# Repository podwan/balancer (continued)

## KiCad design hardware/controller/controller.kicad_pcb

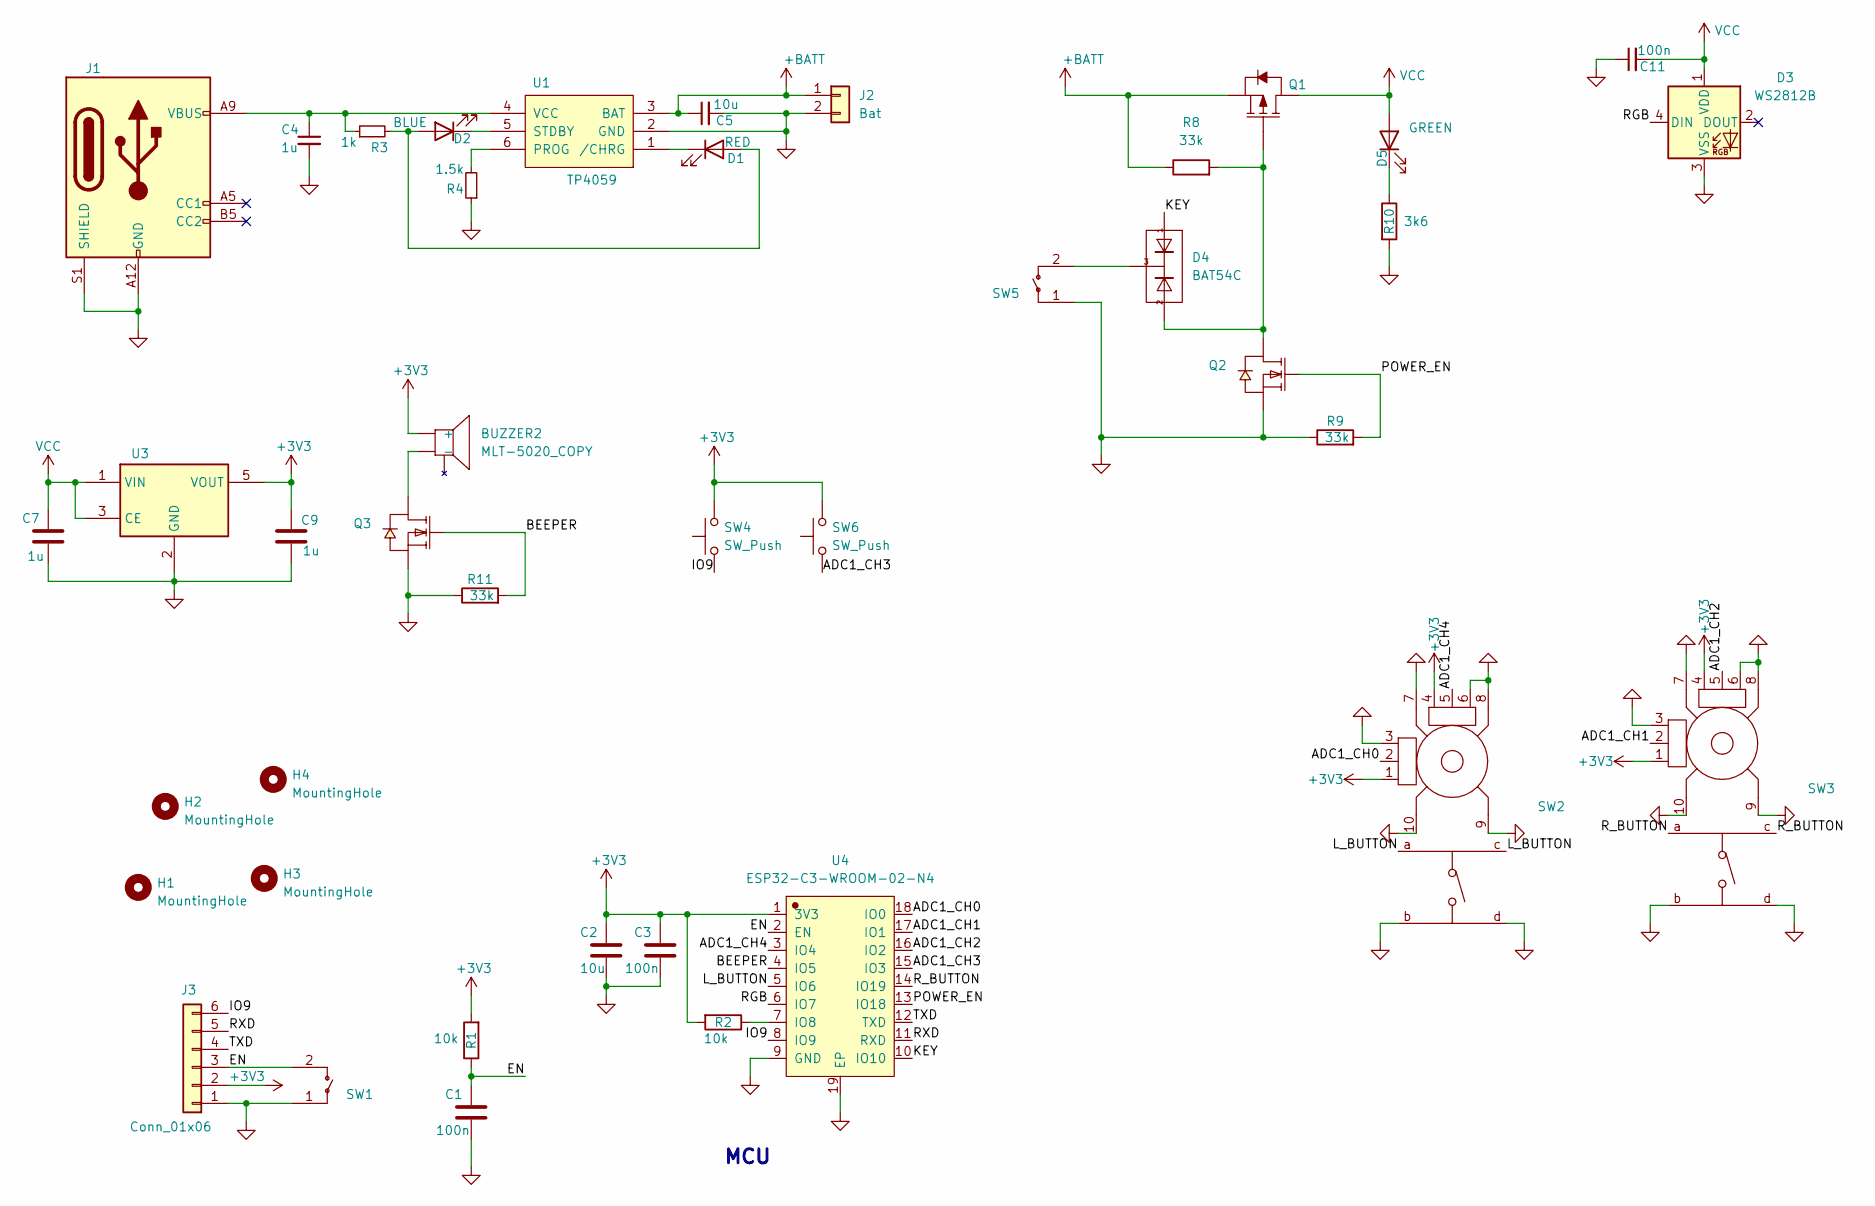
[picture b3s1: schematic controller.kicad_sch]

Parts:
BUZZER2: MLT-5020_COPY; BUZ-SMD_L5.0-W5.5-P4.60
C1, C3, C11: 100n; C_0603_1608Metric_Pad1.08x0.95mm_HandSolder
C2, C5: 10u; C_0805_2012Metric_Pad1.18x1.45mm_HandSolder
C4, C7, C9: 1u; C_0603_1608Metric_Pad1.08x0.95mm_HandSolder
D1: RED; LED_0603_1608Metric_Pad1.05x0.95mm_HandSolder
D2: BLUE; LED_0603_1608Metric_Pad1.05x0.95mm_HandSolder
D3: WS2812B; LED_WS2812B_PLCC4_5.0x5.0mm_P3.2mm
D4: BAT54C; SOT-23
D5: GREEN; LED_0603_1608Metric_Pad1.05x0.95mm_HandSolder
H1, H2, H3, H4: MountingHole; MountingHole_2.2mm_M2_Pad
J1: USB_C_Receptacle_PowerOnly_6P; USB-C-SMD_HX-TYPE-C-6PIN
J2: Bat; CONN-SMD_2P-P2.54-XH2.54-WT
J3: Conn_01x06; CONN-SMD_6P-P1.00_XYECONN_XY-SH1.0-6A61
Q1: AO3401; SOT-23
Q2, Q3: AllPower__AP2300; SOT-23
R1, R2: 10k; R_0603_1608Metric_Pad0.98x0.95mm_HandSolder
R3: 1k; R_0603_1608Metric_Pad0.98x0.95mm_HandSolder
R4: 1.5k; R_0603_1608Metric_Pad0.98x0.95mm_HandSolder
R8, R9, R11: 33k; R_0603_1608Metric_Pad0.98x0.95mm_HandSolder
R10: 3k6; R_0603_1608Metric_Pad0.98x0.95mm_HandSolder
SW1, SW5: TS-1199A-B-B; SW-SMD_L6.0-W6.0-P6.00-LS6.6
SW2, SW3: RKJXV1224005; SW-TH_RKJXV1224005
SW4, SW6: SW_Push
U1: TP4059; SOT-23-6_L2.9-W1.6-P0.95-LS2.8-BR
U3: XC6220B331MR; SOT-23-5
U4: ESP32-C3-WROOM-02-N4; ESP32-C3-WROOM-02

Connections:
+3V3: BUZZER2.1 (+), C2.1, C3.1, C9.1, J3.2, R1.2, R2.2, SW2.1 (B), SW2.4 (A), SW3.1 (B), SW3.4 (A), SW4.2, SW6.2, U3.5 (VOUT), U4.1 (3V3)
+BATT: C5.1, J2.1, Q1.2 (S), R8.1, U1.3 (BAT)
/ADC1_CH0: SW2.2 (DTA), U4.18 (IO0)
/ADC1_CH1: SW3.2 (DTA), U4.17 (IO1)
/ADC1_CH2: SW3.5 (DTA), U4.16 (IO2)
/ADC1_CH3: SW6.1, U4.15 (IO3)
/ADC1_CH4: SW2.5 (DTA), U4.3 (IO4)
/BEEPER: Q3.1 (G), R11.2, U4.4 (IO5)
/EN: C1.1, J3.3, R1.1, SW1.2, U4.2 (EN)
/IO9: J3.6, SW4.1, U4.8 (IO9)
/KEY: D4.1 (A), U4.10 (IO10)
/L_BUTTON: SW2.a, SW2.c, U4.5 (IO6)
/POWER_EN: Q2.1 (G), R9.2, U4.13 (IO18)
/RGB: D3.4 (DIN), U4.6 (IO7)
/RXD: J3.5, U4.11 (RXD)
/R_BUTTON: SW3.a, SW3.c, U4.14 (IO19)
/TXD: J3.4, U4.12 (TXD)
GND: C1.2, C2.2, C3.2, C4.2, C5.2, C7.2, C9.2, C11.1, D3.3 (VSS), J1.A12 (GND), J1.B12 (GND), J1.S1 (SHIELD), J2.2, J3.1, Q2.2 (S), Q3.2 (S), R4.1, R9.1, R10.2, R11.1, SW1.1, SW2.3 (A), SW2.6 (B), SW2.7 (GND), SW2.8 (GND), SW2.9 (GND), SW2.10 (GND), SW2.b, SW2.d, SW3.3 (A), SW3.6 (B), SW3.7 (GND), SW3.8 (GND), SW3.9 (GND), SW3.10 (GND), SW3.b, SW3.d, SW5.1, U1.2 (GND), U3.2 (GND), U4.9 (GND), U4.19 (EP)
unnamed: BUZZER2.2 (-), Q3.3 (D)
unnamed: D1.2 (A), D2.2 (A), R3.2
unnamed: D1.1 (K), U1.1 (/CHRG)
unnamed: D2.1 (K), U1.5 (STDBY)
unnamed: D4.3 (C), SW5.2
unnamed: D5.1 (K), R10.1
unnamed: D4.2 (A), Q1.1 (G), Q2.3 (D), R8.2
unnamed: R4.2, U1.6 (PROG)
unnamed: C4.1, J1.A9 (VBUS), J1.B9 (VBUS), R3.1, U1.4 (VCC)
unnamed: R2.1, U4.7 (IO8)
VCC: C7.1, C11.2, D3.1 (VDD), D5.2 (A), Q1.3 (D), U3.1 (VIN), U3.3 (CE)

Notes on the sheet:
MCU

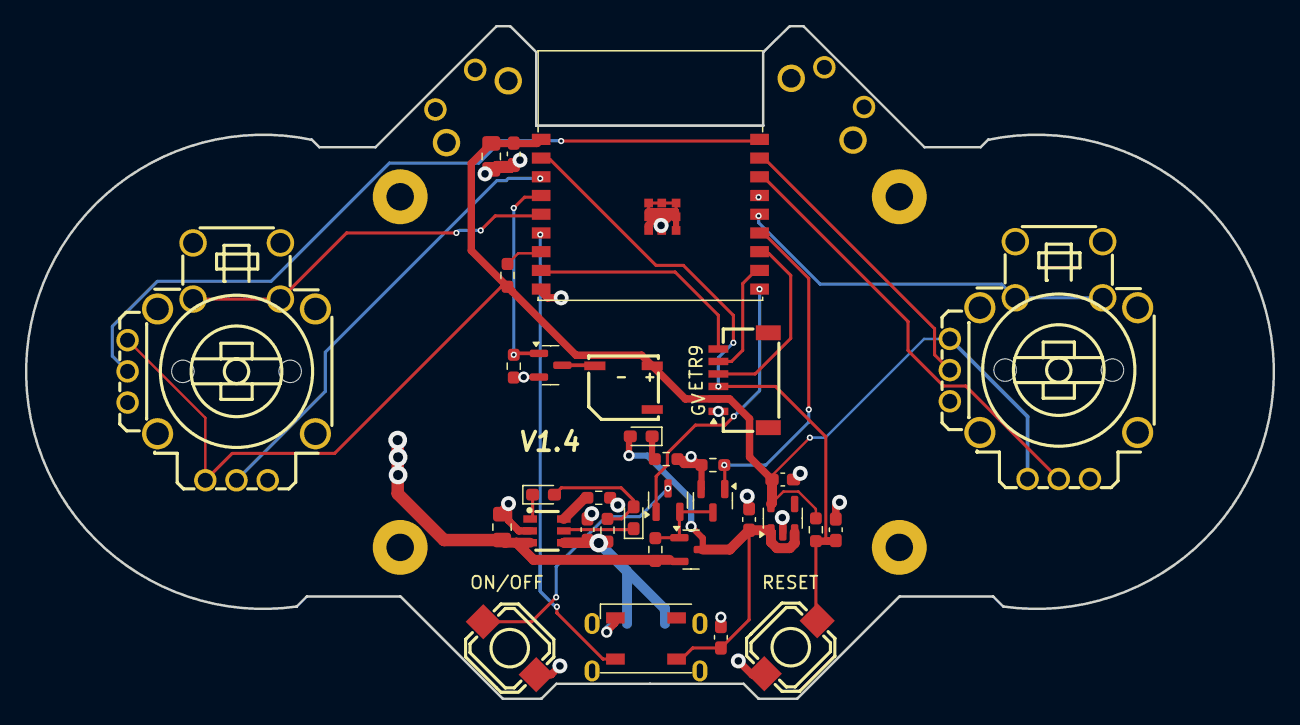
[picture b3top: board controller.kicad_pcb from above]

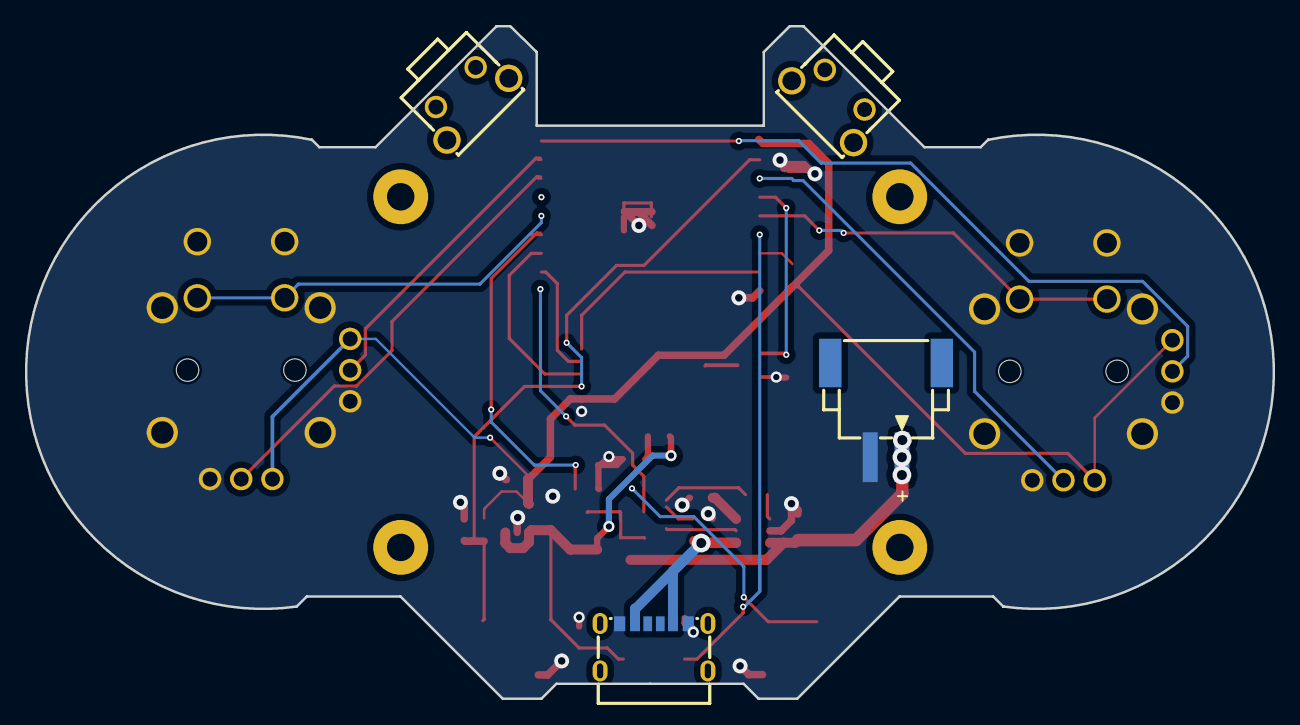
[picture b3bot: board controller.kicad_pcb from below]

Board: 2 copper layers, 100.0 x 53.9 mm, 41 parts (4 on the bottom side), 29 nets.

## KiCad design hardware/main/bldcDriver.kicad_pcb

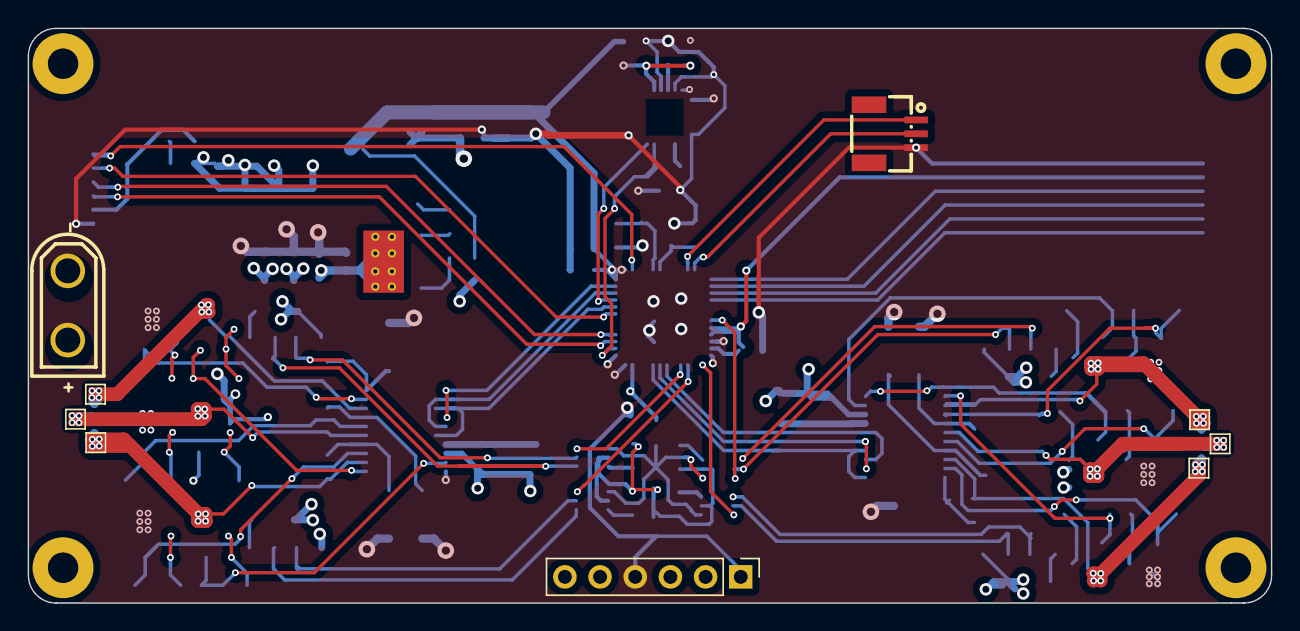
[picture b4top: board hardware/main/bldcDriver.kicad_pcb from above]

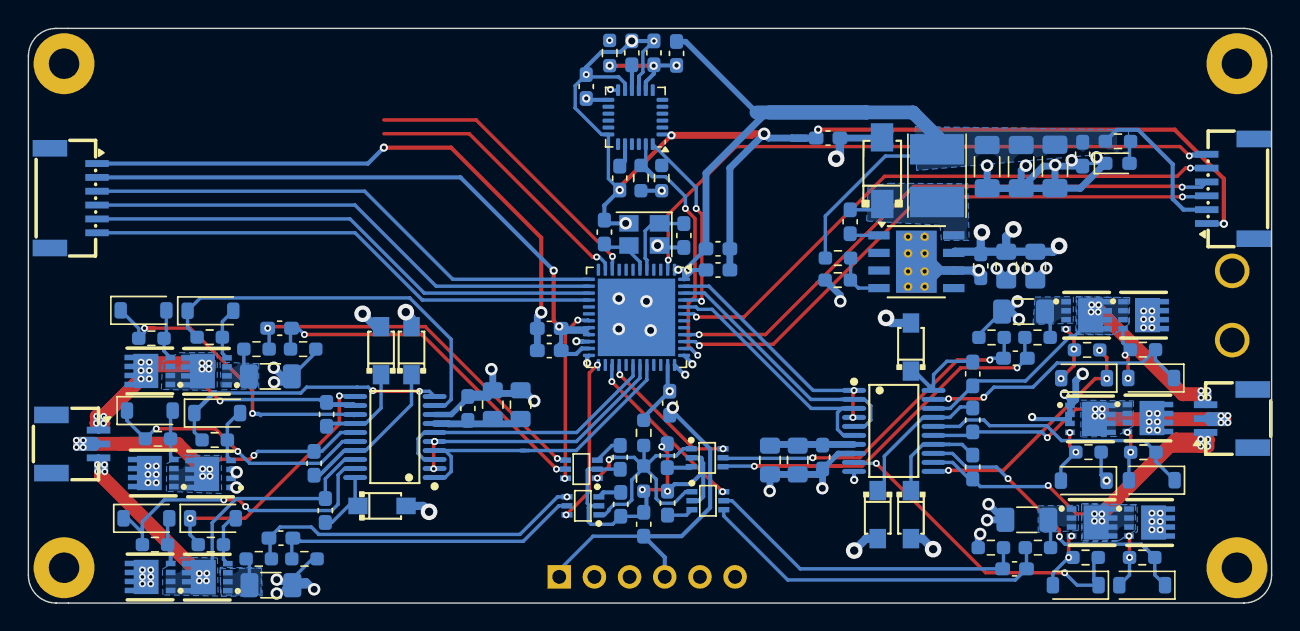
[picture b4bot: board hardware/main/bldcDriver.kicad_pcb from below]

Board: 4 copper layers, 89.8 x 41.5 mm, 130 parts (121 on the bottom side), 96 nets.

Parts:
C1, C13: 10n; C_0603_1608Metric_Pad1.08x0.95mm_HandSolder
C2, C3, C4: 47u; C_1206_3216Metric_Pad1.33x1.80mm_HandSolder
C5, C6, C12, C14, C33, C34: 22u; C_0805_2012Metric_Pad1.18x1.45mm_HandSolder
C7, C8, C9, C10, C11, C15, C16, C17, C18, C19, C20, C22, C23, C25, C26, C27, C29, C30, C31, C32: 100n; C_0603_1608Metric_Pad1.08x0.95mm_HandSolder
C21: 470n; C_0603_1608Metric_Pad1.08x0.95mm_HandSolder
C24: 2.2n; C_0603_1608Metric_Pad1.08x0.95mm_HandSolder
C28, C35, C36, C37: 1n; C_0603_1608Metric_Pad1.08x0.95mm_HandSolder
C67, C68: 12p; C_0603_1608Metric_Pad1.08x0.95mm_HandSolder
CN1, CN2: MR30PW-F; CONN-SMD_3P-P1.00_BX-SH1.0-3PWT
D1: LED; LED_0603_1608Metric_Pad1.05x0.95mm_HandSolder
D2, D3, D4, D7, D10, D11: D; SOD-123FL_L2.7-W1.8-LS3.8-RD
D5, D6, D9, D16, D17, D18, D19, D20, D21, D22, D23, D24: 1N4148W; D_SOD-123
D8: 1N5712UR; SMA_L4.3-W2.6-LS5.0-RD
FB1, FB2, FB3: FerriteBead; C_0603_1608Metric_Pad1.08x0.95mm_HandSolder
J1: Conn_01x02; CONN-TH_XT30UPB-M
J2: Conn_01x06; PinHeader_1x06_P2.54mm_Vertical
J3, J5: Conn_01x06; CONN-SMD_6P-P1.00_MEGASTAR_ZX-SH1.0-6PWT
J4: Conn_01x03; CONN-SMD_3P-P1.00_WAFER-SH1.0-3PWB
L1: 10u; L_Taiyo-Yuden_NR-40xx_HandSoldering
Q1, Q2, Q7, Q8, Q9, Q10, Q11, Q12, Q13, Q14, Q15, Q16: EMB09N03V; POWERTDFN-8_L3.1-W3.1-P0.65-LS3.3-BL
R1, R20, R21, R49: 10k; R_0603_1608Metric_Pad0.98x0.95mm_HandSolder
R2: 5.9k; R_0603_1608Metric_Pad0.98x0.95mm_HandSolder
R3, R72, R73: 4.7k; R_0603_1608Metric_Pad0.98x0.95mm_HandSolder
R4, R5, R6, R7, R8, R13, R14, R15, R16, R17, R18, R19: 10R; R_0603_1608Metric_Pad0.98x0.95mm_HandSolder
R9, R10, R11, R12: 10mR; R_1206_3216Metric_Pad1.30x1.75mm_HandSolder
R22, R23, R24, R25, R26, R27, R28, R29: 100R; R_0603_1608Metric_Pad0.98x0.95mm_HandSolder
TP1, TP2, TP3, TP4, TP5, TP6: TestPoint; TestPoint_Pad_1.0x1.0mm
U1, U2: EG2133; eg2133
U3: TPS5430DDA; TI_SO-PowerPAD-8_ThermalVias
U4: MPU-6050; InvenSense_QFN-24_4x4mm_P0.5mm
U5: STM32G431CBUx; QFN-48-1EP_7x7mm_P0.5mm_EP5.6x5.6mm
U6, U7, U8, U9: TP181A1-CR; SC70-6_L2.1-W1.3-P0.65-LS2.3-BL
Y1: 25MHz; Crystal_SMD_SeikoEpson_FA238-4Pin_3.2x2.5mm

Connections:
+3V3: C2.2, C3.2, C4.2, C8.2, C17.1, C18.1, C19.1, C20.1, C21.1, FB1.1, J2.3, J3.2, J5.2, L1.2, R1.1, R3.1, R20.1, U5.1 (VBAT), U5.20 (VREF+), U5.21 (VDDA), U5.23 (VDD), U5.35 (VDD), U5.48 (VDD)
+BATT: C5.2, C6.2, C7.2, D2.2 (A), D3.2 (A), D4.2 (A), D7.2 (A), D10.2 (A), D11.2 (A), J1.2, Q2.5 (D), Q2.6 (D), Q2.7 (D), Q2.8 (D), Q7.5 (D), Q7.6 (D), Q7.7 (D), Q7.8 (D), Q9.5 (D), Q9.6 (D), Q9.7 (D), Q9.8 (D), Q11.5 (D), Q11.6 (D), Q11.7 (D), Q11.8 (D), Q13.5 (D), Q13.6 (D), Q13.7 (D), Q13.8 (D), Q15.5 (D), Q15.6 (D), Q15.7 (D), Q15.8 (D), U3.7 (VIN)
/1CS1+: C28.2, R22.2, U6.4 (IN+)
/1CS1-: C28.1, R23.2, U6.5 (IN-)
/1CS2+: C35.2, R24.2, U7.4 (IN+)
/1CS2-: C35.1, R25.2, U7.5 (IN-)
/2CS1+: C36.2, R26.2, U8.4 (IN+)
/2CS1-: C36.1, R27.2, U8.5 (IN-)
/2CS2+: C37.2, R28.2, U9.4 (IN+)
/2CS2-: C37.1, R29.2, U9.5 (IN-)
/ADC1_IN5: U5.27 (PB14), U6.6 (OUT)
/ADC1_IN11: U5.25 (PB12), U8.6 (OUT)
/ADC2_IN12: U5.19 (PB2), U9.6 (OUT)
/ADC2_IN15: U5.28 (PB15), U7.6 (OUT)
/I2C1_SCL: R73.2, U4.23 (SCL), U5.38 (PA15)
/I2C1_SDA: R72.2, U4.24 (SDA), U5.45 (PB7)
/MPU_INT: R49.2, U4.12 (INT)
/NSS1: J5.6, U5.2 (PC13)
/NSS2: J3.6, U5.16 (PC4)
/SPI1_MISO: J3.4, U5.14 (PA6)
/SPI1_MOSI: J3.5, U5.15 (PA7)
/SPI1_SCK: J3.3, U5.13 (PA5)
/SPI3_MISO: J5.4, U5.40 (PC11)
/SPI3_MOSI: J5.5, U5.43 (PB5)
/SPI3_SCK: J5.3, U5.39 (PC10)
/SWCLK: J2.6, U5.37 (PA14)
/SWDIO: J2.5, U5.36 (PA13)
/TIM1_CH1: U1.3 (HIN3), U1.6 (LIN3#), U5.30 (PA8)
/TIM1_CH2: U1.2 (HIN2), U1.5 (LIN2#), U5.31 (PA9)
/TIM1_CH3: U1.1 (HIN1), U1.4 (LIN1#), U5.32 (PA10)
/TIM8_CH1: U2.3 (HIN3), U2.6 (LIN3#), U5.44 (PB6)
/TIM8_CH2: U2.2 (HIN2), U2.5 (LIN2#), U5.46 (PB8)
/TIM8_CH3: U2.1 (HIN1), U2.4 (LIN1#), U5.47 (PB9)
/USART2_RX: J4.2, U5.11 (PA3)
/USART2_TX: J4.1, U5.10 (PA2)
/USART3_RX: J2.2, U5.24 (PB11)
/USART3_TX: J2.1, U5.22 (PB10)
/VREF: R20.2, R21.1, U6.1 (REF), U7.1 (REF), U8.1 (REF), U9.1 (REF)
/YI: C67.1, U5.5 (PF0), Y1.1
/YO: C68.1, U5.6 (PF1), Y1.3
/inverter/1HO1: D23.1 (K), R6.1, U2.19 (HO1)
/inverter/1HO2: D9.1 (K), R4.1, U2.16 (HO2)
/inverter/1HO3: D5.1 (K), R8.1, U2.13 (HO3)
/inverter/1LO1: D24.1 (K), R19.1, U2.11 (LO1)
/inverter/1LO2: D22.1 (K), R5.1, U2.10 (LO2)
/inverter/1LO3: D6.1 (K), R7.1, U2.9 (LO3)
/inverter/1VS1: C29.2, CN1.3, Q15.1 (S), Q15.2 (S), Q15.3 (S), Q16.5 (D), Q16.6 (D), Q16.7 (D), Q16.8 (D), TP3.1, U2.18 (VS1)
/inverter/1VS2: C30.2, CN1.2, Q2.1 (S), Q2.2 (S), Q2.3 (S), Q14.5 (D), Q14.6 (D), Q14.7 (D), Q14.8 (D), TP2.1, U2.15 (VS2)
/inverter/1VS3: C31.2, CN1.1, Q1.5 (D), Q1.6 (D), Q1.7 (D), Q1.8 (D), Q13.1 (S), Q13.2 (S), Q13.3 (S), TP1.1, U2.12 (VS3)
/inverter/2HO1: D16.1 (K), R13.1, U1.19 (HO1)
/inverter/2HO2: D18.1 (K), R15.1, U1.16 (HO2)
/inverter/2HO3: D20.1 (K), R17.1, U1.13 (HO3)
/inverter/2LO1: D17.1 (K), R14.1, U1.11 (LO1)
/inverter/2LO2: D19.1 (K), R16.1, U1.10 (LO2)
/inverter/2LO3: D21.1 (K), R18.1, U1.9 (LO3)
/inverter/2VS1: C16.2, CN2.3, Q7.1 (S), Q7.2 (S), Q7.3 (S), Q8.5 (D), Q8.6 (D), Q8.7 (D), Q8.8 (D), TP6.1, U1.18 (VS1)
/inverter/2VS2: C25.2, CN2.2, Q9.1 (S), Q9.2 (S), Q9.3 (S), Q10.5 (D), Q10.6 (D), Q10.7 (D), Q10.8 (D), TP5.1, U1.15 (VS2)
/inverter/2VS3: C26.2, CN2.1, Q11.1 (S), Q11.2 (S), Q11.3 (S), Q12.5 (D), Q12.6 (D), Q12.7 (D), Q12.8 (D), TP4.1, U1.12 (VS3)
GNDA: C9.1, C10.1, C11.1, C27.1, FB3.1, R21.2, U6.2 (GND), U7.2 (GND), U8.2 (GND), U9.2 (GND)
GNDD: C13.2, C17.2, C18.2, C19.2, C20.2, C21.2, C22.2, C23.2, C24.2, C67.2, C68.2, FB2.2, FB3.2, J2.4, J3.1, J4.3, J5.1, U4.1 (CLKIN), U4.9 (AD0), U4.11 (FSYNC), U4.18 (GND), U5.49 (VSS), Y1.2, Y1.4
GNDPWR: C2.1, C3.1, C4.1, C5.1, C6.1, C7.1, C8.1, C12.2, C14.2, C15.2, C32.2, C33.2, C34.2, D1.1 (K), D8.2 (A), FB2.1, J1.1, Q10.1 (S), Q10.2 (S), Q10.3 (S), Q14.1 (S), Q14.2 (S), Q14.3 (S), R2.2, R9.1, R10.1, R11.1, R12.1, R23.1, R25.1, R27.1, R29.1, U1.8 (GND), U2.8 (GND), U3.6 (GND), U3.9 (GNDPAD)
unnamed: D1.2 (A), R3.2
unnamed: C16.1, D2.1 (K), U1.20 (VB1)
unnamed: C25.1, D3.1 (K), U1.17 (VB2)
unnamed: C26.1, D4.1 (K), U1.14 (VB3)
unnamed: D5.2 (A), Q13.4 (G), R8.2
unnamed: D6.2 (A), Q1.4 (G), R7.2
unnamed: C29.1, D7.1 (K), U2.20 (VB1)
unnamed: C1.2, D8.1 (K), L1.1, U3.8 (PH)
unnamed: D9.2 (A), Q2.4 (G), R4.2
unnamed: C30.1, D10.1 (K), U2.17 (VB2)
unnamed: C31.1, D11.1 (K), U2.14 (VB3)
unnamed: D16.2 (A), Q7.4 (G), R13.2
unnamed: D17.2 (A), Q8.4 (G), R14.2
unnamed: D18.2 (A), Q9.4 (G), R15.2
unnamed: D19.2 (A), Q10.4 (G), R16.2
unnamed: D20.2 (A), Q11.4 (G), R17.2
unnamed: D21.2 (A), Q12.4 (G), R18.2
unnamed: D22.2 (A), Q14.4 (G), R5.2
unnamed: D23.2 (A), Q15.4 (G), R6.2
unnamed: D24.2 (A), Q16.4 (G), R19.2
unnamed: Q1.1 (S), Q1.2 (S), Q1.3 (S), R9.2, R22.1
unnamed: Q8.1 (S), Q8.2 (S), Q8.3 (S), R11.2, R26.1
unnamed: Q12.1 (S), Q12.2 (S), Q12.3 (S), R12.2, R28.1
unnamed: Q16.1 (S), Q16.2 (S), Q16.3 (S), R10.2, R24.1
unnamed: C12.1, C14.1, C15.1, U1.7 (VCC)
unnamed: C32.1, C33.1, C34.1, U2.7 (VCC)
unnamed: C1.1, U3.1 (BOOT)
unnamed: R1.2, R2.1, U3.4 (VSENSE)
unnamed: C24.1, U4.20 (CPOUT)
unnamed: C23.1, U4.10 (REGOUT)
unnamed: C13.1, C22.1, FB1.2, R49.1, R72.1, R73.1, U4.8 (VLOGIC), U4.13 (VDD)
unnamed: C9.2, U6.3 (V+)
unnamed: C10.2, U7.3 (V+)
unnamed: C11.2, U8.3 (V+)
unnamed: C27.2, U9.3 (V+)

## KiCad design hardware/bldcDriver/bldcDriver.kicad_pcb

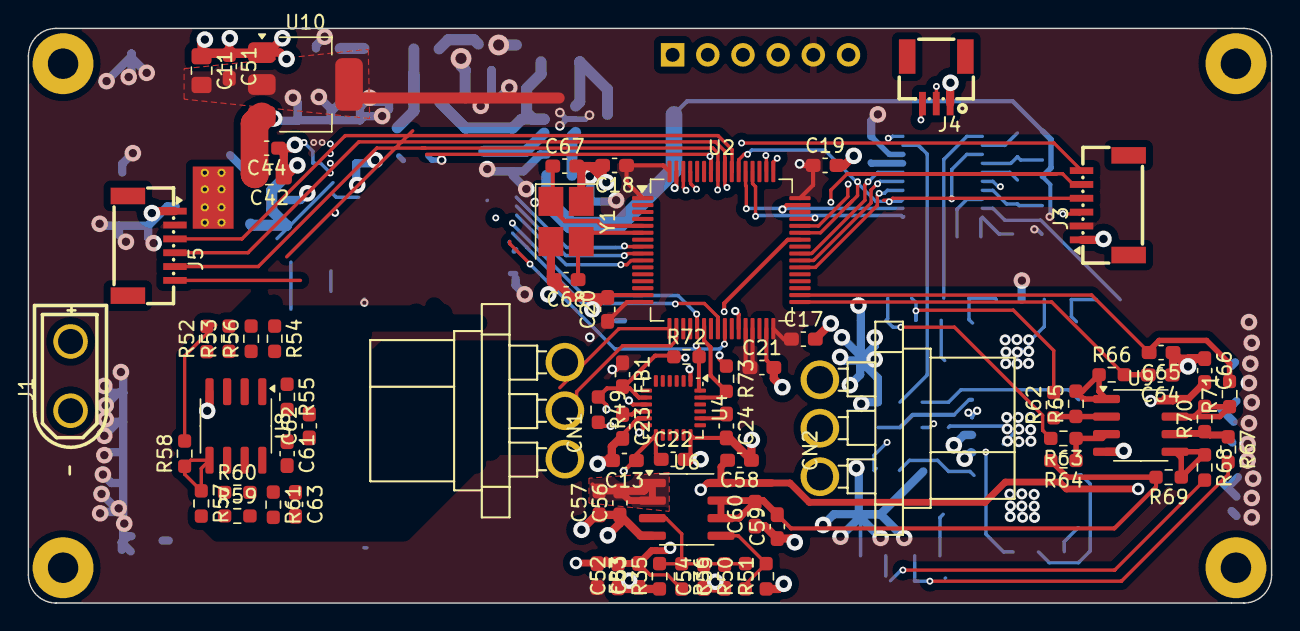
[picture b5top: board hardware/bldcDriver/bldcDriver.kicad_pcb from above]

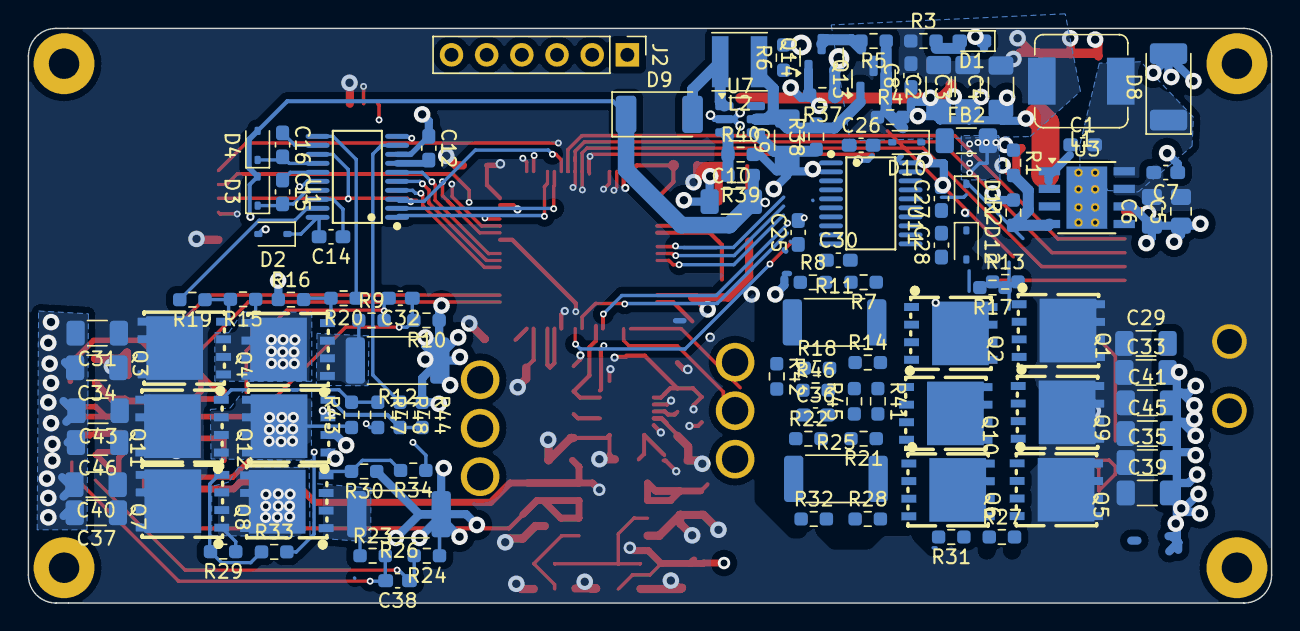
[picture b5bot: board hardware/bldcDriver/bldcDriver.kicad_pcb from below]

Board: 4 copper layers, 89.8 x 41.5 mm, 183 parts (111 on the bottom side), 119 nets.

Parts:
C1, C13: 10n; C_0603_1608Metric_Pad1.08x0.95mm_HandSolder
C2, C3, C4, C9, C10: 47u; C_1206_3216Metric_Pad1.33x1.80mm_HandSolder
C5, C6: 22u; C_0805_2012Metric_Pad1.18x1.45mm_HandSolder
C7, C8, C14, C15, C16, C17, C18, C19, C20, C22, C23, C26, C27, C28, C44, C51, C53, C55, C57, C58, C60, C61, C66: 100n; C_0603_1608Metric_Pad1.08x0.95mm_HandSolder
C11, C42: 10u; C_0805_2012Metric_Pad1.18x1.45mm_HandSolder
C12, C25: 100nF/25V; C_0603_1608Metric_Pad1.08x0.95mm_HandSolder
C21: 470n; C_0603_1608Metric_Pad1.08x0.95mm_HandSolder
C24, C62, C63, C64, C65: 2.2n; C_0603_1608Metric_Pad1.08x0.95mm_HandSolder
C29, C31, C33, C34, C35, C37, C39, C40, C41, C43, C45, C46: 22uF/25V; C_1206_3216Metric_Pad1.33x1.80mm_HandSolder
C30, C32, C36, C38: 1n; C_0603_1608Metric_Pad1.08x0.95mm_HandSolder
C52, C54, C56, C59: 4.7u; C_0603_1608Metric_Pad1.08x0.95mm_HandSolder
C67, C68: 12p; C_0603_1608Metric_Pad1.08x0.95mm_HandSolder
CN1, CN2: MR30PW-F; CONN-TH_MR30PW-F
D1: LED; LED_0603_1608Metric_Pad1.05x0.95mm_HandSolder
D2, D3, D4, D10, D11, D12: 1N5819WS; D_SOD-323
D8, D9: 1N5712UR; D_MELF
FB1, FB3: FerriteBead; C_0603_1608Metric_Pad1.08x0.95mm_HandSolder
FB2: FerriteBead; C_1206_3216Metric_Pad1.33x1.80mm_HandSolder
J1: Conn_01x02; CONN-TH_XT30UPB-M
J2: Conn_01x06; PinHeader_1x06_P2.54mm_Vertical
J3, J5: Conn_01x06; CONN-SMD_6P-P1.00_MEGASTAR_ZX-SH1.0-6PWT
J4: Conn_01x03; CONN-SMD_3P-P1.00_WAFER-SH1.0-3PWB
L1: 10u; L_Sumida_CDMC6D28_7.25x6.5mm
L2: 10u; L_Taiyo-Yuden_MD-4040
Q1, Q2, Q3, Q4, Q5, Q6, Q7, Q8, Q9, Q10, Q11, Q12: KNY3406C; PDFN-8_L4.9-W5.8-P1.27-LS6.1-BL
Q13: PMOS; SOT-23
Q14: S8050; SOT-23
R1, R4, R13, R14, R15, R16, R27, R28, R29, R30, R37, R38, R41, R42, R43, R44, R49, R52, R54, R58, R60, R64, R65, R69, R70: 10k; R_0603_1608Metric_Pad0.98x0.95mm_HandSolder
R2, R40: 3.3k; R_0603_1608Metric_Pad0.98x0.95mm_HandSolder
R3, R72, R73: 4.7k; R_0603_1608Metric_Pad0.98x0.95mm_HandSolder
R5, R7, R8, R9, R10, R21, R22, R23, R24, R55, R61, R66, R71: 100R; R_0603_1608Metric_Pad0.98x0.95mm_HandSolder
R6, R35, R36, R50, R51, R53, R56, R57, R59, R62, R63, R67, R68: 1k; R_0603_1608Metric_Pad0.98x0.95mm_HandSolder
R11, R12, R25, R26: 20mR; R_2512_6332Metric_Pad1.40x3.35mm_HandSolder
R17, R18, R19, R20, R31, R32, R33, R34, R45, R46, R47, R48: 10R; R_0603_1608Metric_Pad0.98x0.95mm_HandSolder
R39: 63.4k; R_0603_1608Metric_Pad0.98x0.95mm_HandSolder
U1, U11: FD6288T; TSSOP-20_L6.5-W4.4-P0.65-LS6.4-BL
U2: STM32G431RBTx; LQFP-64_10x10mm_P0.5mm
U3: TPS5430DDA; TI_SO-PowerPAD-8_ThermalVias
U4: MPU-6050; InvenSense_QFN-24_4x4mm_P0.5mm
U6, U8, U9: TLV9062xD; SOIC-8_3.9x4.9mm_P1.27mm
U7: MT3608; SOT-23-6
U10: AMS1117; SOT-223-3_TabPin2
Y1: 25MHz; Crystal_SMD_SeikoEpson_FA238-4Pin_3.2x2.5mm_HandSoldering

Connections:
+3V3: C11.2, C17.1, C18.1, C19.1, C20.1, C21.1, C51.2, FB1.1, FB3.2, J2.5, J3.2, J5.2, U2.1 (VBAT), U2.16 (VDD), U2.28 (VREF+), U2.29 (VDDA), U2.32 (VDD), U2.48 (VDD), U2.64 (VDD), U10.2 (VO)
+5V: C2.2, C3.2, C4.2, C8.2, C42.2, C44.2, L1.2, Q13.3 (S), R1.1, R3.1, R4.1, U10.3 (VI)
+12V: C10.2, D2.2 (A), D3.2 (A), D4.2 (A), D9.1 (K), D10.2 (A), D11.2 (A), D12.2 (A), R39.1
+BATT: C5.2, C6.2, C7.2, C29.1, C31.1, C33.1, C34.1, C35.1, C37.1, C39.1, C40.1, C41.1, C43.1, C45.1, C46.1, J1.2, Q1.5 (D), Q1.6 (D), Q1.7 (D), Q1.8 (D), Q1.9 (D), Q3.5 (D), Q3.6 (D), Q3.7 (D), Q3.8 (D), Q3.9 (D), Q5.5 (D), Q5.6 (D), Q5.7 (D), Q5.8 (D), Q5.9 (D), Q7.5 (D), Q7.6 (D), Q7.7 (D), Q7.8 (D), Q7.9 (D), Q9.5 (D), Q9.6 (D), Q9.7 (D), Q9.8 (D), Q9.9 (D), Q11.5 (D), Q11.6 (D), Q11.7 (D), Q11.8 (D), Q11.9 (D), U3.7 (VIN)
/1A_ISENSOR+: C30.2, R7.2, R56.2
/1A_ISENSOR-: C30.1, R8.2, R53.2
/1B_ISENSOR+: C36.2, R21.2, R59.2
/1B_ISENSOR-: C36.1, R22.2, R57.2
/2A_ISENSOR+: C32.2, R9.2, R62.2
/2A_ISENSOR-: C32.1, R10.2, R63.2
/2B_ISENSOR+: C38.2, R23.2, R67.2
/2B_ISENSOR-: C38.1, R24.2, R68.2
/I2C2_SCL: R73.2, U2.22 (PC4), U4.23 (SCL)
/I2C2_SDA: R72.2, U2.42 (PA8), U4.24 (SDA)
/INA1+: C54.2, C55.2, R35.2, R36.1, R50.2, U6.3 (+)
/INA2+: R50.1, R51.2, U6.5 (+)
/M1_ADC1_IN4: C62.2, R55.2, U2.17 (PA3)
/M1_ADC2_IN7: C63.2, R61.2, U2.18 (PA4)
/M2_ADC1_IN11: C65.2, R71.2, U2.34 (PB12)
/M2_ADC2_IN14: C64.2, R66.2, U2.33 (PB11)
/MPU_INT: R49.2, U4.12 (INT)
/NSS1: J5.3, U2.55 (PD2)
/NSS2: J3.3, U2.45 (PA11)
/OP_VCC: C52.2, C53.2, C58.2, C61.2, C66.2, FB3.1, R36.2, U6.8 (V+), U8.8 (V+), U9.8 (V+)
/SPI1_MISO: J3.5, J5.5, U2.57 (PB4)
/SPI1_MOSI: J3.6, J5.6, U2.58 (PB5)
/SPI1_SCK: J3.4, J5.4, U2.56 (PB3)
/SWCLK: J2.4, U2.50 (PA14)
/SWDIO: J2.3, U2.49 (PA13)
/TIM1_CH1: U2.8 (PC0), U11.1 (HIN1)
/TIM1_CH1N: U2.21 (PA7), U11.4 (LIN1)
/TIM1_CH2: U2.9 (PC1), U11.2 (HIN2)
/TIM1_CH2N: U2.24 (PB0), U11.5 (LIN2)
/TIM1_CH3: U2.10 (PC2), U11.3 (HIN3)
/TIM1_CH3N: U2.25 (PB1), U11.6 (LIN3)
/TIM8_CH1: U1.4 (LIN1), U2.38 (PC6)
/TIM8_CH1N: U1.1 (HIN1), U2.52 (PC10)
/TIM8_CH2: U1.5 (LIN2), U2.39 (PC7)
/TIM8_CH2N: U1.2 (HIN2), U2.53 (PC11)
/TIM8_CH3: U1.6 (LIN3), U2.40 (PC8)
/TIM8_CH3N: U1.3 (HIN3), U2.54 (PC12)
/USART1_RX: J4.2, U2.44 (PA10)
/USART1_TX: J4.3, U2.43 (PA9)
/USART3_RX: J2.1, U2.61 (PB8)
/USART3_TX: J2.2, U2.62 (PB9)
/VREF_OP1: C56.2, C57.2, R52.2, R58.2, U6.1, U6.2 (-)
/VREF_OP2: C59.2, C60.2, R64.2, R69.2, U6.6 (-), U6.7
/YI: C67.1, U2.5 (PF0), Y1.1
/YO: C68.1, U2.6 (PF1), Y1.3
/inverter/1GH_A: R17.2, U11.19 (HO1)
/inverter/1GH_B: R31.2, U11.16 (HO2)
/inverter/1GH_C: R45.2, U11.13 (HO3)
/inverter/1GL_A: R18.1, U11.11 (LO1)
/inverter/1GL_B: R32.1, U11.10 (LO2)
/inverter/1GL_C: R46.1, U11.9 (LO3)
/inverter/1SH_U: C26.1, CN1.1, Q1.1 (S), Q1.2 (S), Q1.3 (S), Q2.5 (D), Q2.6 (D), Q2.7 (D), Q2.8 (D), Q2.9 (D), R13.1, U11.18 (VS1)
/inverter/1SH_V: C27.1, CN1.2, Q9.1 (S), Q9.2 (S), Q9.3 (S), Q10.5 (D), Q10.6 (D), Q10.7 (D), Q10.8 (D), Q10.9 (D), R41.1, U11.15 (VS2)
/inverter/1SH_W: C28.1, CN1.3, Q5.1 (S), Q5.2 (S), Q5.3 (S), Q6.5 (D), Q6.6 (D), Q6.7 (D), Q6.8 (D), Q6.9 (D), R27.1, U11.12 (VS3)
/inverter/1VB1: C26.2, D10.1 (K), U11.20 (VB1)
/inverter/1VB2: C27.2, D11.1 (K), U11.17 (VB2)
/inverter/1VB3: C28.2, D12.1 (K), U11.14 (VB3)
/inverter/2GH_A: R19.2, U1.19 (HO1)
/inverter/2GH_B: R33.2, U1.16 (HO2)
/inverter/2GH_C: R47.2, U1.13 (HO3)
/inverter/2GL_A: R20.1, U1.11 (LO1)
/inverter/2GL_B: R34.1, U1.10 (LO2)
/inverter/2GL_C: R48.1, U1.9 (LO3)
/inverter/2SH_U: C14.1, CN2.3, Q3.1 (S), Q3.2 (S), Q3.3 (S), Q4.5 (D), Q4.6 (D), Q4.7 (D), Q4.8 (D), Q4.9 (D), R15.1, U1.18 (VS1)
/inverter/2SH_V: C15.1, CN2.2, Q11.1 (S), Q11.2 (S), Q11.3 (S), Q12.5 (D), Q12.6 (D), Q12.7 (D), Q12.8 (D), Q12.9 (D), R43.1, U1.15 (VS2)
/inverter/2SH_W: C16.1, CN2.1, Q7.1 (S), Q7.2 (S), Q7.3 (S), Q8.5 (D), Q8.6 (D), Q8.7 (D), Q8.8 (D), Q8.9 (D), R29.1, U1.12 (VS3)
/inverter/2VB1: C14.2, D2.1 (K), U1.20 (VB1)
/inverter/2VB2: C15.2, D3.1 (K), U1.17 (VB2)
/inverter/2VB3: C16.2, D4.1 (K), U1.14 (VB3)
GNDD: C11.1, C13.2, C17.2, C18.2, C19.2, C20.2, C21.2, C22.2, C23.2, C24.2, C42.1, C44.1, C51.1, C52.1, C53.1, C54.1, C55.1, C56.1, C57.1, C58.1, C59.1, C60.1, C61.1, C62.1, C63.1, C64.1, C65.1, C66.1, C67.2, C68.2, FB2.2, J2.6, J3.1, J4.1, J5.1, R35.1, R51.1, U2.15 (VSS), U2.27 (VSSA), U2.31 (VSS), U2.47 (VSS), U2.63 (VSS), U4.1 (CLKIN), U4.9 (AD0), U4.11 (FSYNC), U4.18 (GND), U6.4 (V-), U8.4 (V-), U9.4 (V-), U10.1 (ADJ), Y1.2, Y1.4
GNDPWR: C2.1, C3.1, C4.1, C5.1, C6.1, C7.1, C8.1, C9.1, C10.1, C12.1, C25.1, C29.2, C31.2, C33.2, C34.2, C35.2, C37.2, C39.2, C40.2, C41.2, C43.2, C45.2, C46.2, D1.1 (K), D8.2 (A), FB2.1, J1.1, Q10.1 (S), Q10.2 (S), Q10.3 (S), Q12.1 (S), Q12.2 (S), Q12.3 (S), Q14.1 (E), R2.2, R8.1, R10.1, R11.1, R12.1, R14.1, R16.1, R22.1, R24.1, R25.1, R26.1, R28.1, R30.1, R37.2, R40.2, R42.1, R44.1, U1.8 (COM), U3.6 (GND), U3.9 (GNDPAD), U7.2 (GND), U11.8 (COM)
unnamed: D1.2 (A), R3.2
unnamed: C1.2, D8.1 (K), L1.1, U3.8 (PH)
unnamed: D9.2 (A), L2.2, U7.1 (SW)
unnamed: Q1.4 (G), R13.2, R17.1
unnamed: Q2.4 (G), R14.2, R18.2
unnamed: Q2.1 (S), Q2.2 (S), Q2.3 (S), R7.1, R11.2
unnamed: Q3.4 (G), R15.2, R19.1
unnamed: Q4.4 (G), R16.2, R20.2
unnamed: Q4.1 (S), Q4.2 (S), Q4.3 (S), R9.1, R12.2
unnamed: Q5.4 (G), R27.2, R31.1
unnamed: Q6.4 (G), R28.2, R32.2
unnamed: Q6.1 (S), Q6.2 (S), Q6.3 (S), R21.1, R25.2
unnamed: Q7.4 (G), R29.2, R33.1
unnamed: Q8.4 (G), R30.2, R34.2
unnamed: Q8.1 (S), Q8.2 (S), Q8.3 (S), R23.1, R26.2
unnamed: Q9.4 (G), R41.2, R45.1
unnamed: Q10.4 (G), R42.2, R46.2
unnamed: Q11.4 (G), R43.2, R47.1
unnamed: Q12.4 (G), R44.2, R48.2
unnamed: C9.2, L2.1, Q13.1 (D), R38.2, U7.5 (IN)
unnamed: Q13.2 (G), R4.2, R5.1
unnamed: Q14.2 (B), R6.2, R37.1
unnamed: Q14.3 (C), R5.2
unnamed: R54.2, R55.1, U8.1
unnamed: R60.2, R61.1, U8.7
unnamed: R65.2, R66.1, U9.1
unnamed: R70.2, R71.1, U9.7
unnamed: C12.2, U1.7 (VCC)
unnamed: C1.1, U3.1 (BOOT)
unnamed: R1.2, R2.1, U3.4 (VSENSE)
unnamed: C24.1, U4.20 (CPOUT)
unnamed: C23.1, U4.10 (REGOUT)
unnamed: C13.1, C22.1, FB1.2, R49.1, R72.1, R73.1, U4.8 (VLOGIC), U4.13 (VDD)
unnamed: R38.1, U7.4 (EN)
unnamed: R39.2, R40.1, U7.3 (FB)
unnamed: R52.1, R53.1, U8.3 (+)
unnamed: R54.1, R56.1, U8.2 (-)
unnamed: R57.1, R58.1, U8.5 (+)
unnamed: R59.1, R60.1, U8.6 (-)
unnamed: R63.1, R64.1, U9.3 (+)
unnamed: R62.1, R65.1, U9.2 (-)
unnamed: R68.1, R69.1, U9.5 (+)
unnamed: R67.1, R70.1, U9.6 (-)
unnamed: C25.2, U11.7 (VCC)

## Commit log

2023-12-03 hardware init
2023-12-03 add readme
2023-12-03 hardwere_init
2023-12-03 hardwere_edit
2023-12-03 edit readme
2023-12-03 hardware update
2023-12-03 hardware edit
2023-12-03 add githubWorkflow
2023-12-03 文件整理
2023-12-04 加入充电电路
2023-12-16 esp32 sch update
2023-12-17 rfBat PCB sent to manufacturing
2023-12-19 espBat update
2023-12-22 bldcDriver sch update
2023-12-31 driver sch update
2024-01-01 batRf to v1.1
2024-01-06 paused for preparing foc with sensor
2024-02-19 更换充电芯片
2024-03-01 更新rfBat PCB
2024-03-24 update espBat
2024-03-25 update rfBat
2024-03-26 “update”
2024-03-27 update rfBat pcb
2024-03-28 rfBat ready to manufacture
2024-04-03 motor sch update
2024-04-04 motorDriver sch update
2024-04-05 update motorDriver sch
2024-04-06 update driver pcb
2024-04-07 update pcbs
2024-04-08 motorDriver pcb update
2024-04-08 update motorDriver pcb
2024-04-09 update driver pcn
2024-04-10 update rfBat firmware
2024-04-20 update mechanic
2024-04-22 update controller sch
2024-04-22 update controller pcb
2024-04-23 update body
2024-04-28 update motor pcb
2024-05-02 update rfBat firmware auto reconnection needed
2024-05-10 update pcb
2024-05-12 update controller firmware
2024-05-14 update motor firmware
2024-05-27 update pcn
2024-06-10 update ibom
2024-06-10 update espBat firmware
2024-06-11 udpate controller pcb
2024-06-15 upate motor firmware
2024-06-23 update motor
2024-06-25 update firmware
2024-07-04 update controller
2024-07-07 update bat PCB
2024-07-13 udpate ble firmware
2024-07-20 udpate motor firmware
2024-07-23 udpate firmware
2024-07-23 电压初步性能
2024-07-24 电压性能版
2024-07-25 seal
2024-07-25 sealed
2024-07-25 add images
